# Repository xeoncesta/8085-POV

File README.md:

# 8085-POV
Assembly Code and hardware implementation for 8085 MPU based POV Display.

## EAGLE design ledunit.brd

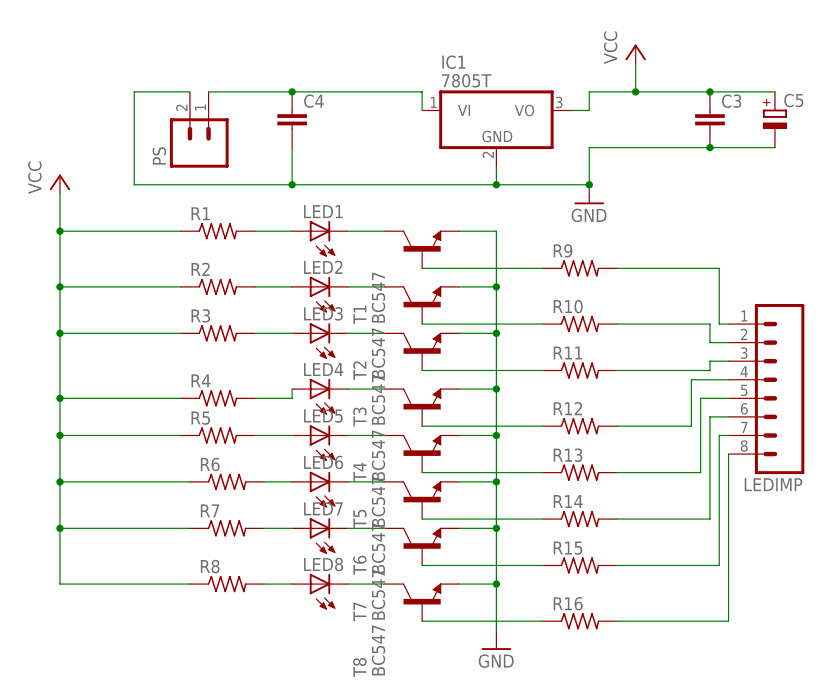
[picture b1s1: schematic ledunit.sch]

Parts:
C3, C4: C-EU025-024X044; C025-024X044
C5: CPOL-EUE2,5-6E; E2,5-6E
IC1: 7805T; TO220H
LED1, LED2, LED3, LED4, LED5, LED6, LED7, LED8: LED5MM
LEDIMP: M08; 08P
PS: M02; 02P
R1, R2, R3, R4, R5, R6, R7, R8, R9, R10, R11, R12, R13, R14, R15, R16: R-US_0204/7; 0204/7
T1, T2, T3, T4, T5, T6, T7, T8: BC547; TO92

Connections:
GND: C3.2, C4.2, C5.-, IC1.2 (GND), PS.2, T1.1 (E), T2.1 (E), T3.1 (E), T4.1 (E), T5.1 (E), T6.1 (E), T7.1 (E), T8.1 (E)
unnamed: LED8.A, R8.2
unnamed: LED7.A, R7.2
unnamed: LED6.A, R6.2
unnamed: LED5.A, R5.2
unnamed: LED4.A, R4.2
unnamed: LED3.A, R3.2
unnamed: LED2.A, R2.2
unnamed: LED1.A, R1.2
unnamed: LED1.K (C), T1.3 (C)
unnamed: LED2.K (C), T2.3 (C)
unnamed: LED3.K (C), T3.3 (C)
unnamed: LED4.K (C), T4.3 (C)
unnamed: LED5.K (C), T5.3 (C)
unnamed: LED6.K (C), T6.3 (C)
unnamed: LED7.K (C), T7.3 (C)
unnamed: LED8.K (C), T8.3 (C)
unnamed: R9.1, T1.2 (B)
unnamed: R10.1, T2.2 (B)
unnamed: R11.1, T3.2 (B)
unnamed: R12.1, T4.2 (B)
unnamed: R13.1, T5.2 (B)
unnamed: R14.1, T6.2 (B)
unnamed: R15.1, T7.2 (B)
unnamed: R16.1, T8.2 (B)
unnamed: LEDIMP.1, R9.2
unnamed: LEDIMP.2, R10.2
unnamed: LEDIMP.3, R11.2
unnamed: LEDIMP.4, R12.2
unnamed: LEDIMP.5, R13.2
unnamed: LEDIMP.6, R14.2
unnamed: LEDIMP.7, R15.2
unnamed: LEDIMP.8, R16.2
unnamed: C4.1, IC1.1 (VI), PS.1
VCC: C3.1, C5.+, IC1.3 (VO), R1.1, R2.1, R3.1, R4.1, R5.1, R6.1, R7.1, R8.1

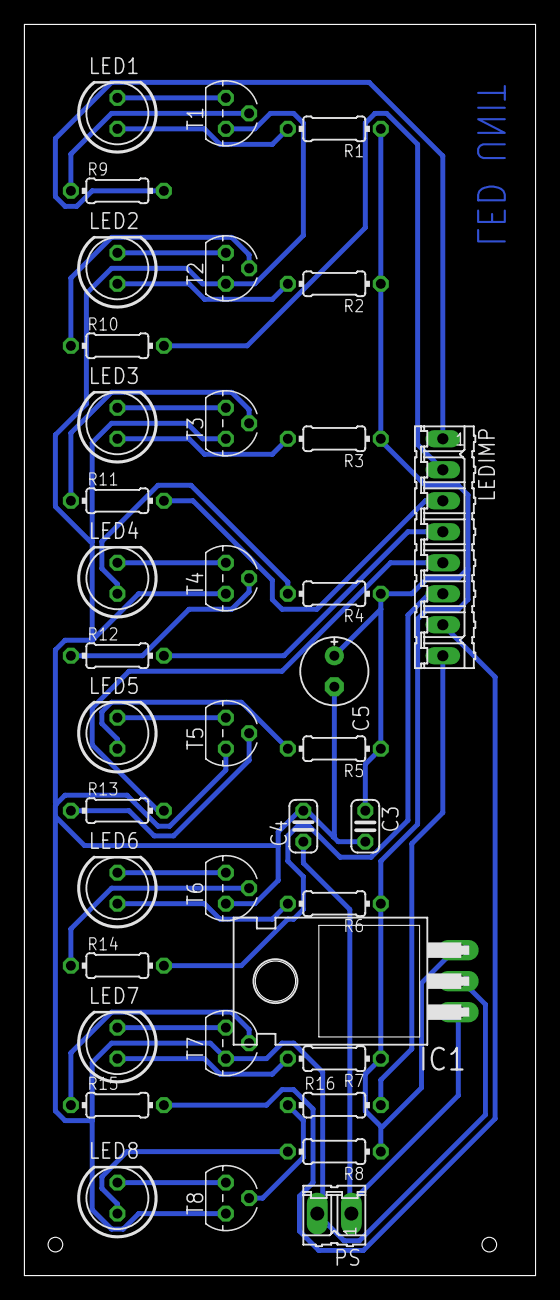
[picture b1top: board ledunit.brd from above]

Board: 2 copper layers, 41.9 x 102.5 mm, 38 parts (0 on the bottom side), 35 nets.

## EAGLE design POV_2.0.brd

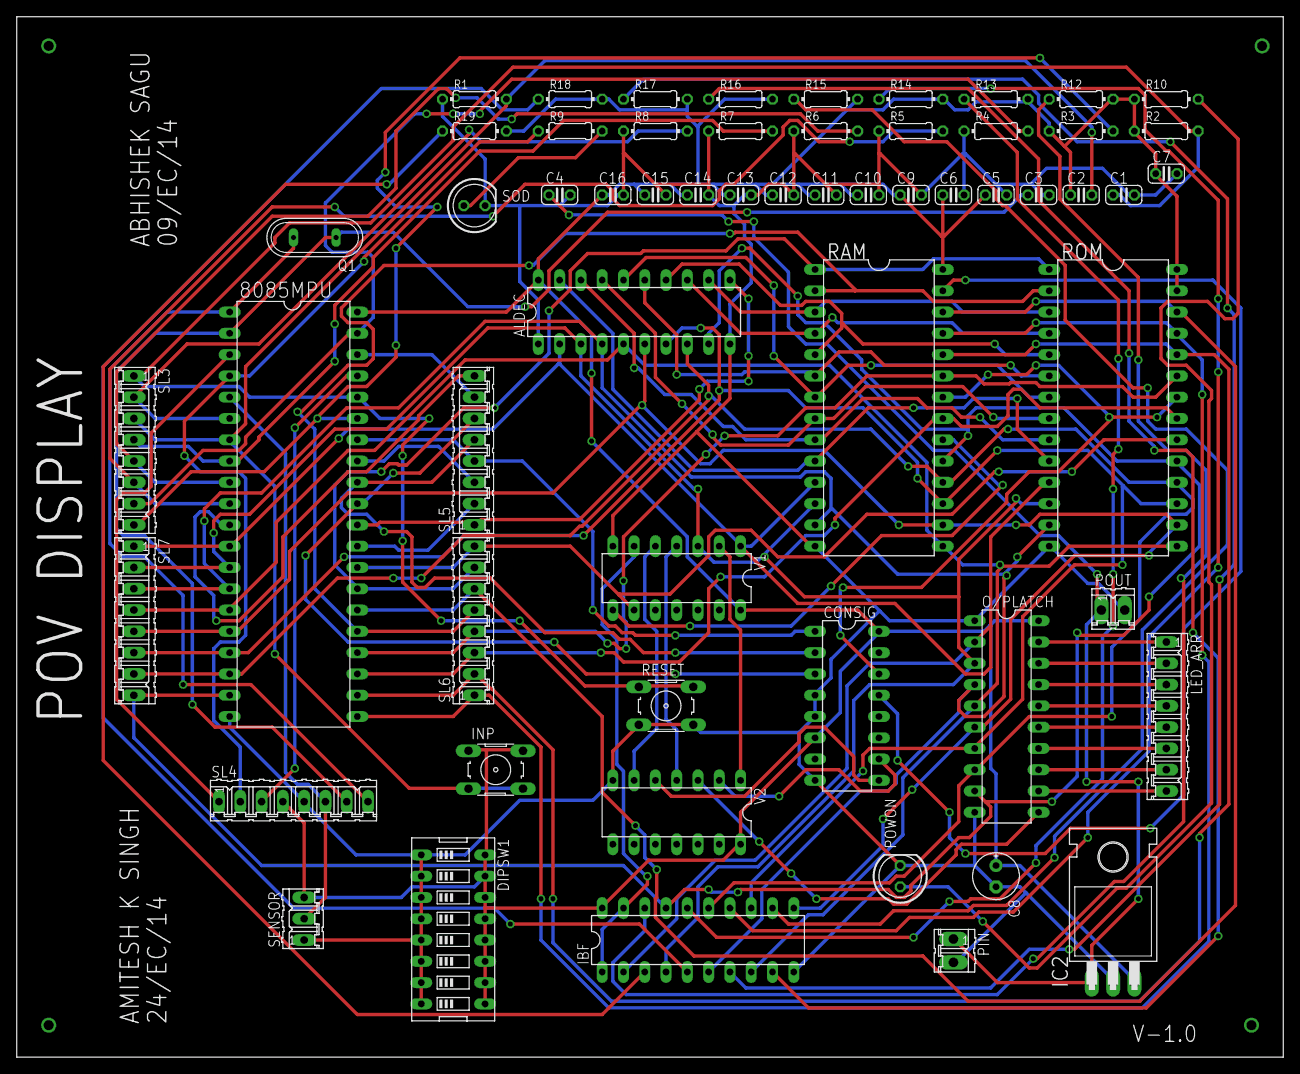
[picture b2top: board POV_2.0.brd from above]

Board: 2 copper layers, 151.1 x 124.1 mm, 59 parts (0 on the bottom side), 77 nets.

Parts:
8085MPU: DIL40
ALDEC: 74HCT573N; DIL20
C1, C2, C3, C5, C6, C9, C10, C11, C12, C13, C14, C15, C16: C025-024X044
C4, C7: 0.01uF; C025-024X044
C8: 10uF; E2,5-6E
CONSIG: 74HCT138N; DIL16
DIPSW1: EDG-08
IBF: 74HCT244N; DIL20
IC2: 7805T; TO220H
INP: B3F-10XX
LED_ARR: 08P
O/PLATCH: 74HCT573N; DIL20
PIN: 02P
POUT: 02P
POWON: LED5MM
Q1: QS
R1, R2, R3, R4, R5, R6, R7, R8, R9, R10, R12, R13, R14, R15, R16, R17, R18, R19: 0204/7
RAM: DIL28-6
RESET: B3F-10XX
ROM: DIL28-6
SENSOR: 03P
SL3, SL4, SL5, SL6, SL7: 08P
SOD: LED5MM
V1: 7404N; DIL14
V2: 74HCT00N; DIL14

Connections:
A8: 8085MPU.21, RAM.25, ROM.25, SL6.1
A9: 8085MPU.22, RAM.24, ROM.24, SL6.2
A10: 8085MPU.23, RAM.21, ROM.21, SL6.3
A11: 8085MPU.24, RAM.23, ROM.23, SL6.4
A12: 8085MPU.25, RAM.2, ROM.2, SL6.5
A13: 8085MPU.26, RAM.26, ROM.26, SL6.6
A14: 8085MPU.27, RAM.1, ROM.1, SL6.7
A15: 8085MPU.28, ROM.20, SL6.8, V1.9
AD0: 8085MPU.12, ALDEC.2, IBF.2, O/PLATCH.2, RAM.11, ROM.11, SL7.1, V1.1
AD1: 8085MPU.13, ALDEC.3, IBF.4, O/PLATCH.3, RAM.12, ROM.12, SL7.2, V1.3
AD2: 8085MPU.14, ALDEC.4, IBF.6, O/PLATCH.4, RAM.13, ROM.13, SL7.3
AD3: 8085MPU.15, ALDEC.5, IBF.8, O/PLATCH.5, RAM.15, ROM.15, SL7.4
AD4: 8085MPU.16, ALDEC.6, IBF.11, O/PLATCH.6, RAM.16, ROM.16, SL7.5
AD5: 8085MPU.17, ALDEC.7, IBF.13, O/PLATCH.7, RAM.17, ROM.17, SL7.6
AD6: 8085MPU.18, ALDEC.8, IBF.15, O/PLATCH.8, RAM.18, ROM.18, SL7.7
AD7: 8085MPU.19, ALDEC.9, IBF.17, O/PLATCH.9, RAM.19, ROM.19, SL7.8
ALE: 8085MPU.30, ALDEC.11, SL5.1
CA15: RAM.20, V1.8
CLK: 8085MPU.37, SL4.3
GND: 8085MPU.20, ALDEC.1, ALDEC.10, C1.2, C3.2, C4.2, C5.2, C6.2, C7.2, C8.-, C9.2, C10.2, C11.2, C12.2, C13.2, C14.2, C15.2, C16.2, CONSIG.4, CONSIG.5, CONSIG.8, DIPSW1.1, DIPSW1.2, DIPSW1.3, DIPSW1.4, DIPSW1.5, DIPSW1.6, DIPSW1.7, DIPSW1.8, IBF.10, IC2.2, O/PLATCH.1, O/PLATCH.10, PIN.2, POUT.2, POWON.K, R1.1, R4.1, R5.1, R6.1, R7.1, R8.1, RAM.14, RESET.3, RESET.4, ROM.14, SENSOR.1, SL4.5, SOD.K, V1.7, V2.7
HLDA: 8085MPU.38, SL5.7
HOLD: 8085MPU.39, R4.2, SL3.7
INTA: 8085MPU.11, SL5.8
INTR: 8085MPU.10, R5.2, SL3.6
IO/M: 8085MPU.34, CONSIG.1, SL5.4
IOR: CONSIG.9, V2.5
IOW: CONSIG.10, V2.2
IPBE: V1.5, V2.6
MR: CONSIG.14, RAM.22, ROM.22
MW: CONSIG.13, RAM.27
unnamed: LED_ARR.1, O/PLATCH.19
unnamed: LED_ARR.2, O/PLATCH.18
unnamed: LED_ARR.3, O/PLATCH.17
unnamed: LED_ARR.4, O/PLATCH.16
unnamed: LED_ARR.5, O/PLATCH.15
unnamed: LED_ARR.6, O/PLATCH.14
unnamed: LED_ARR.7, O/PLATCH.13
unnamed: LED_ARR.8, O/PLATCH.12
unnamed: ALDEC.19, RAM.10, ROM.10
unnamed: ALDEC.18, RAM.9, ROM.9
unnamed: ALDEC.17, RAM.8, ROM.8
unnamed: ALDEC.16, RAM.7, ROM.7
unnamed: ALDEC.15, RAM.6, ROM.6
unnamed: ALDEC.14, RAM.5, ROM.5
unnamed: ALDEC.13, RAM.4, ROM.4
unnamed: ALDEC.12, RAM.3, ROM.3
unnamed: IBF.18, R12.1
unnamed: IBF.16, R13.1
unnamed: IBF.14, R14.1
unnamed: IBF.12, R15.1
unnamed: IBF.9, R16.1
unnamed: IBF.7, R17.1
unnamed: IBF.5, R18.1
unnamed: IBF.1, IBF.19, V1.6
unnamed: IBF.3, R19.1
unnamed: R9.2, SOD.A
unnamed: C4.1, IC2.1, PIN.1, POUT.1
unnamed: POWON.A, R10.2
unnamed: V1.2, V2.1
unnamed: V1.4, V2.4
OPLE: O/PLATCH.11, V2.3
RD: 8085MPU.32, CONSIG.2, SL5.5
READY: 8085MPU.35, R3.2, SL3.8
RES_IN: 8085MPU.36, C1.1, R2.2, RESET.1, RESET.2, SL3.1
RES_OUT: 8085MPU.3, SL4.1
RST5.5: 8085MPU.9, R6.2, SL3.5
RST6.5: 8085MPU.8, R7.2, SL3.4
RST7.5: 8085MPU.7, C2.2, INP.3, INP.4, R1.2, SL3.3
S0: 8085MPU.29, SL5.2
S1: 8085MPU.33, SL5.3
SID: 8085MPU.5, SENSOR.2, SL4.6
SOD: 8085MPU.4, R9.1, SL4.2
TRAP: 8085MPU.6, R8.2, SL3.2
VCC: 8085MPU.40, ALDEC.20, C2.1, C5.1, C6.1, C7.1, C8.+, C9.1, C10.1, C11.1, C12.1, C13.1, C14.1, C15.1, C16.1, CONSIG.6, CONSIG.16, DIPSW1.9, DIPSW1.10, DIPSW1.11, DIPSW1.12, DIPSW1.13, DIPSW1.14, DIPSW1.15, DIPSW1.16, IBF.20, IC2.3, INP.1, INP.2, O/PLATCH.20, R2.1, R3.1, R10.1, R12.2, R13.2, R14.2, R15.2, R16.2, R17.2, R18.2, R19.2, RAM.28, ROM.27, ROM.28, SENSOR.3, SL4.4, V1.14, V2.14
WR: 8085MPU.31, CONSIG.3, SL5.6
X1: 8085MPU.1, Q1.2, SL4.8
X2: 8085MPU.2, C3.1, Q1.1, SL4.7

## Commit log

2017-04-02 Proposal
2017-05-22 Board File
2017-05-22 Schematic File
    Open in Eagle CAD
2017-05-22 External Unit
    Add external unit as per need.
2017-05-22 Images
    A few images and working videos.
2017-05-22 ASSEMBLY CODE FOR 8085 MPU
    Assembly Code for the POV display unit.
2017-05-22 Set theme jekyll-theme-hacker
